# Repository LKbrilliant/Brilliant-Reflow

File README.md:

# Brilliant-Reflow
A complete DIY solution for converting a consumer oven into a temperature controlled reflow oven for PCB soldering.

.png)
.png)

https://github.com/user-attachments/assets/c0d352e0-495b-4052-a3d3-c1c6e0b2d40d

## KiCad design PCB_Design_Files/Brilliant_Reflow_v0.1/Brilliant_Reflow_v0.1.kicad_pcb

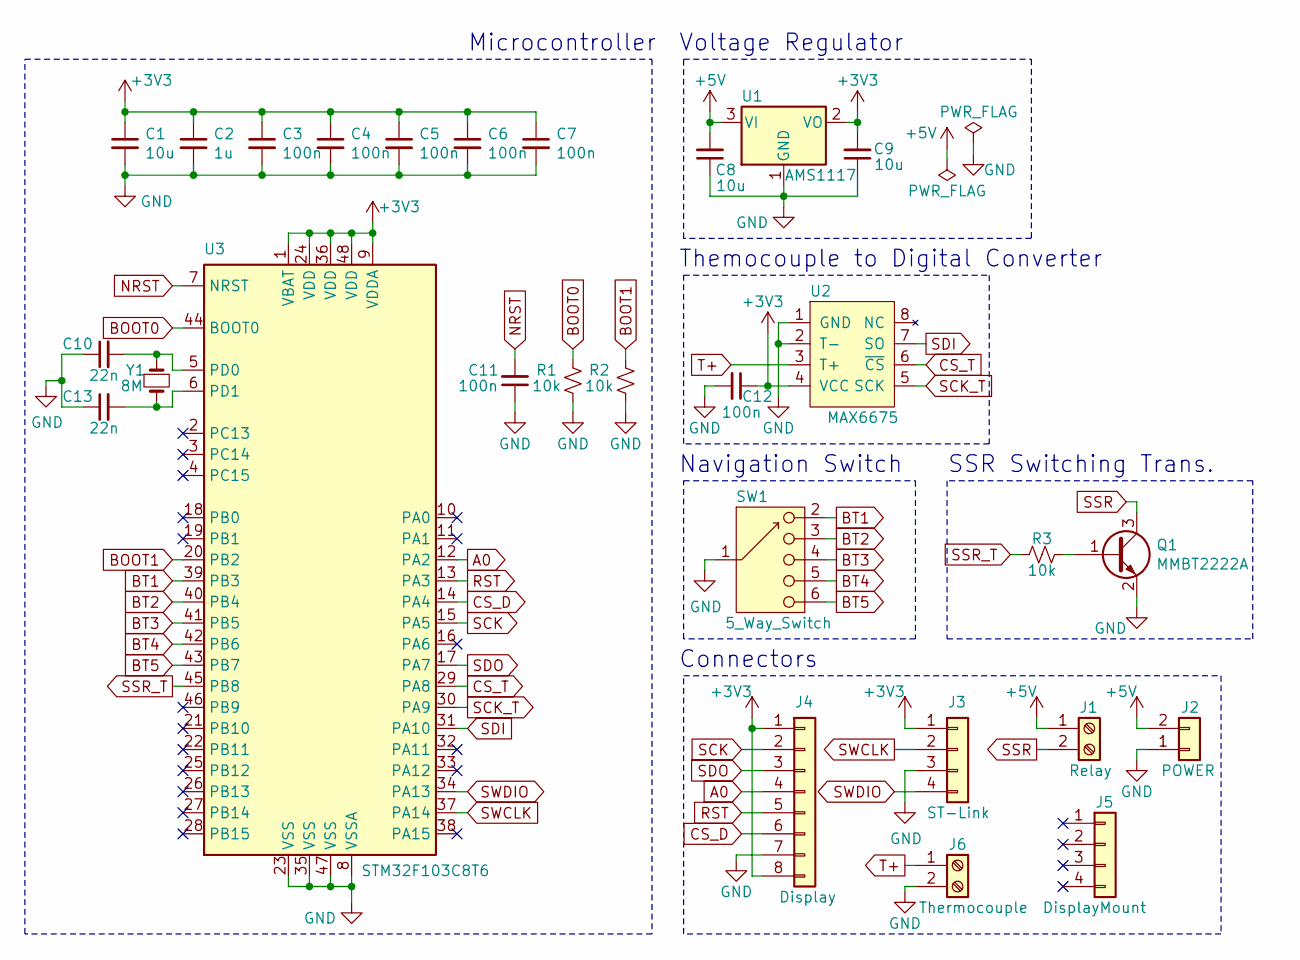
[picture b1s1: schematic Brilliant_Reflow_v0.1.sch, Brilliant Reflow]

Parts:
C1, C8, C9: 10u; C_0603_1608Metric
C2: 1u; C_0603_1608Metric
C3, C4, C5, C6, C7, C11, C12: 100n; C_0603_1608Metric
C10, C13: 22n; C_0603_1608Metric
J1: Relay; TerminalBlock_bornier-2_P5.08mm
J2: POWER; PinHeader_1x02_P2.54mm_Vertical
J3: ST-Link; PinHeader_1x04_P2.54mm_Vertical
J4: Display; PinSocket_1x08_P2.54mm_Vertical
J5: DisplayMount; PinSocket_1x04_P2.54mm_Vertical
J6: Thermocouple; TerminalBlock_7.62mm_2p
Q1: MMBT2222A; SOT-23
R1, R2, R3: 10k; R_0603_1608Metric
SW1: 5_Way_Switch
U1: AMS1117; SOT-223-3_TabPin2
U2: MAX6675; SO-8_3.9x4.9mm_P1.27mm
U3: STM32F103C8T6; LQFP-48_7x7mm_P0.5mm
Y1: 8M; Crystal_SMD_HC49-SD

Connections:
+3V3: C1.1, C2.1, C3.1, C4.1, C5.1, C6.1, C7.1, C9.2, C12.1, J3.1, J4.1, J4.8, U1.2 (VO), U2.4 (VCC), U3.1 (VBAT), U3.9 (VDDA), U3.24 (VDD), U3.36 (VDD), U3.48 (VDD)
+5V: C8.2, J1.1, J2.2, U1.3 (VI)
A0: J4.4, U3.12 (PA2)
BOOT0: R1.1, U3.44 (BOOT0)
BOOT1: R2.1, U3.20 (PB2)
BT1: SW1.2, U3.39 (PB3)
BT2: SW1.3, U3.40 (PB4)
BT3: SW1.4, U3.41 (PB5)
BT4: SW1.5, U3.42 (PB6)
BT5: SW1.6, U3.43 (PB7)
CS_D: J4.6, U3.14 (PA4)
CS_T: U2.6 (~CS), U3.29 (PA8)
GND: C1.2, C2.2, C3.2, C4.2, C5.2, C6.2, C7.2, C8.1, C9.1, C10.1, C11.1, C12.2, C13.1, J2.1, J3.3, J4.7, J6.2, Q1.2 (E), R1.2, R2.2, SW1.1, U1.1 (GND), U2.1 (GND), U2.2 (T-), U3.8 (VSSA), U3.23 (VSS), U3.35 (VSS), U3.47 (VSS)
NRST: C11.2, U3.7 (NRST)
unnamed: C10.2, U3.5 (PD0), Y1.1
unnamed: C13.2, U3.6 (PD1), Y1.2
unnamed: Q1.1 (B), R3.1
RST: J4.5, U3.13 (PA3)
SCK: J4.2, U3.15 (PA5)
SCK_T: U2.5 (SCK), U3.30 (PA9)
SDI: U2.7 (SO), U3.31 (PA10)
SDO: J4.3, U3.17 (PA7)
SSR: J1.2, Q1.3 (C)
SSR_T: R3.2, U3.45 (PB8)
SWCLK: J3.2, U3.37 (PA14)
SWDIO: J3.4, U3.34 (PA13)
T+: J6.1, U2.3 (T+)

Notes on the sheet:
Microcontroller
Themocouple to Digital Converter
Voltage Regulator
Navigation Switch
Connectors
SSR Switching Trans.

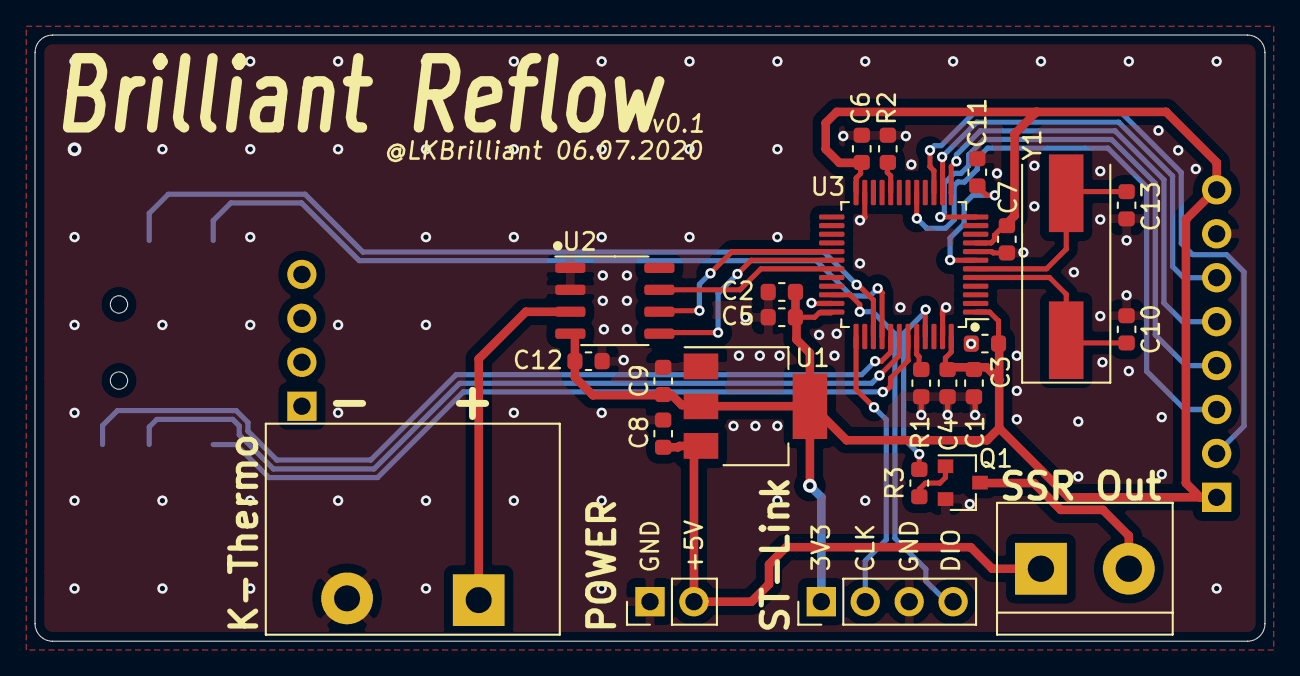
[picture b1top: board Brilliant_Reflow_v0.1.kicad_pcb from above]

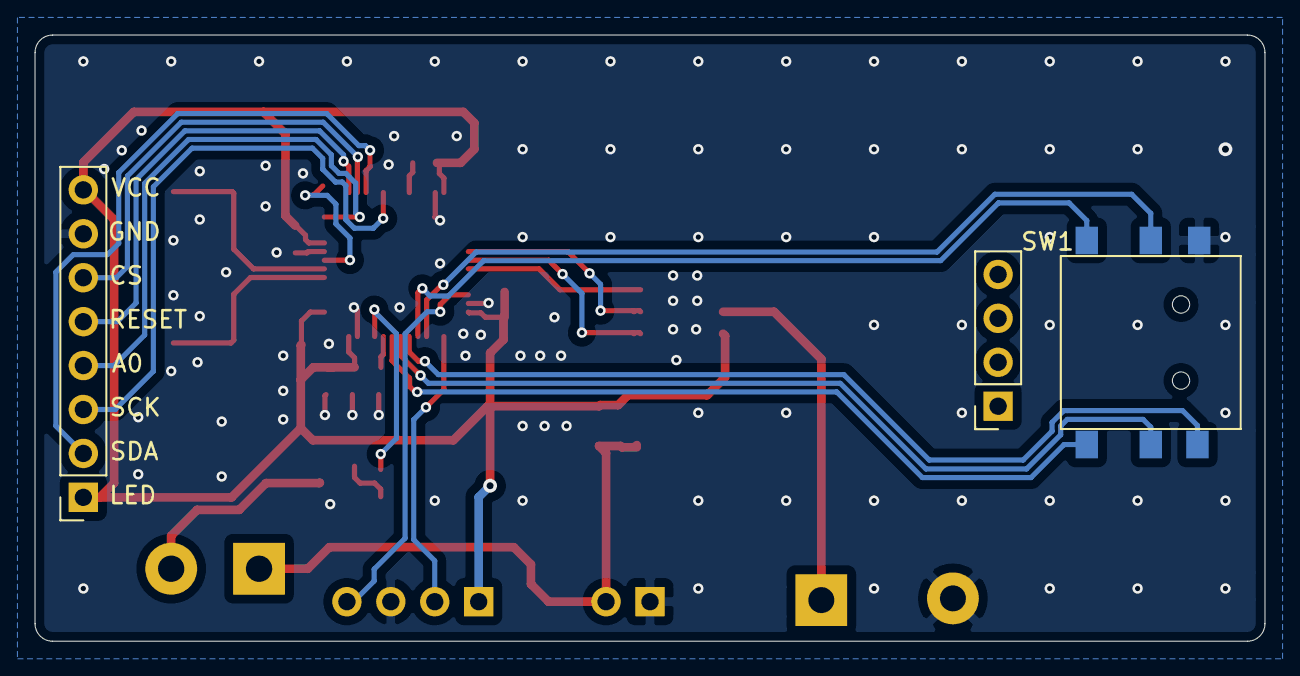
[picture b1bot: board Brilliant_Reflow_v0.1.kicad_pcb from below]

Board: 2 copper layers, 71.1 x 35.1 mm, 28 parts (3 on the bottom side), 27 nets.

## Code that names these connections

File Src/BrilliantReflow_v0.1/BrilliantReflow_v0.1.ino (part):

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#define blackOnYellow 201
#define yellowOnBlack 202

#define SSR_out PB8

#define btnDebounceDelay 200
#define tempSampleRate 200

Ucglib_ST7735_18x128x160_HWSPI ucg(PA2, PA4, PA3);
MAX6675 thermocouple(PA9, PA8, PA10);

bool debug = true;        // Show PID output info on the disply when heating

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volatile unsigned long lstBtnBounce = 0;

void setup(void) {
  pinMode(PB3, INPUT_PULLUP);
  pinMode(PB4, INPUT_PULLUP);
  pinMode(PB5, INPUT_PULLUP);
  pinMode(PB6, INPUT_PULLUP);
  pinMode(PB7, INPUT_PULLUP);
  pinMode(PB8, OUTPUT);

  attachInterrupt(digitalPinToInterrupt(PB3), up, FALLING);
  attachInterrupt(digitalPinToInterrupt(PB4), center, RISING);
  attachInterrupt(digitalPinToInterrupt(PB5), right, FALLING);
  attachInterrupt(digitalPinToInterrupt(PB6), down, FALLING);
  attachInterrupt(digitalPinToInterrupt(PB7), left, FALLING);

  ucg.begin(UCG_FONT_MODE_SOLID);
  ucg.setFontPosBaseline();
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
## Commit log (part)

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2021-11-05 Add KiCAD gitignore
2021-11-05 Change LICENSE
2021-11-05 Add PCB Design and Fabrication files
2021-11-05 Add firmware
2021-11-05 Add Media
2021-11-05 Update media
2021-11-05 Change image resolution
2022-01-30 Add PID debug info toggle
2022-01-30 Added fast value change when pressing and holding
2022-01-30 version update
2022-01-30 Add release binary v1.0.0
2022-06-23 Upload CAD files
